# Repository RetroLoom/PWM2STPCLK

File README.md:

# PWM2STPCLK
Vintage CPU throttle adapter designed for use with interchangable PWM controllers. 

This project is inspired from the ThrottleBlaster project from Scrap Computing.

https://github.com/scrapcomputing/ThrottleBlaster

The PWM2STPCLK can mount directly to an ATX motherboard stand-off for direct chassis grounding and securing. This allows placement of the STPCLK pin wiring to be close to CPU and guarded from strain. A standard PWM fan controller can be used for simplicity, but plans for developing dedicated controllers and adapting the ThrottleBlaster is on-going. 

## Build of Materials
https://github.com/RetroLoom/PWM2STPCLK/blob/master/KiCad/PWM2STPCLK.csv

Example PWM Controller - https://www.aliexpress.us/item/3256805787442361.html?spm=a2g0o.order_list.order_list_main.71.628f1802pm9FhH&gatewayAdapt=glo2usa

Example PWM Cables - https://www.aliexpress.us/item/3256805588566722.html?spm=a2g0o.order_list.order_list_main.77.628f1802pm9FhH&gatewayAdapt=glo2usa

## Support the Developer
This project is brought to you free and open source, but it is not free to develop. If you like this project please consider supporting this and future developments. 

https://www.patreon.com/RetroLoom

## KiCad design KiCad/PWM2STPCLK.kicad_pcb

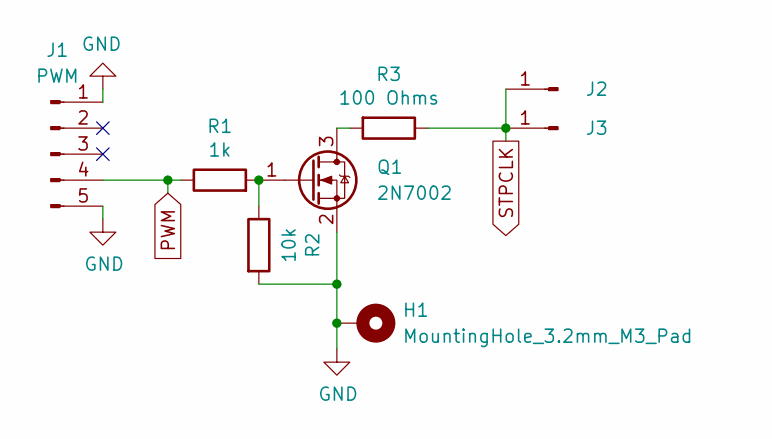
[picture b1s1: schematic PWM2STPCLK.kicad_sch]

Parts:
H1: MountingHole_3.2mm_M3_Pad
J1: PWM; PinSocket_1x05_P2.54mm_Vertical
J2, J3: STPCLK; PinHeader_1x01_P2.54mm_Horizontal
Q1: 2N7002; SOT-23
R1: 1k; R_0805_2012Metric
R2: 10k; R_0805_2012Metric
R3: 100 Ohms; R_0805_2012Metric

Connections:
GND: H1.1, J1.1, J1.5, Q1.2 (S), R2.2
unnamed: Q1.3 (D), R3.2
unnamed: Q1.1 (G), R1.2, R2.1
PWM: J1.4, R1.1
STPCLK: J2.1, J3.1, R3.1

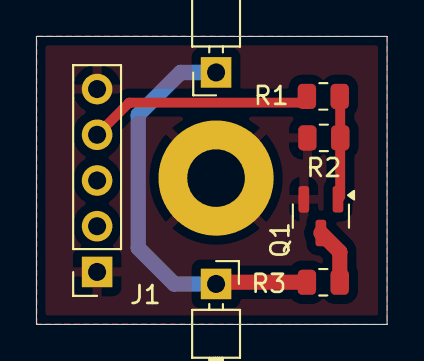
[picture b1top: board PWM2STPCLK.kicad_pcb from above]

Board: 2 copper layers, 19.5 x 16.0 mm, 8 parts (0 on the bottom side), 5 nets.

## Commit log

2025-01-30 Initial Release
2025-01-31 Update Readme, Images, License
2025-01-31 Fix broken readme images
2025-02-24 v0.2 - Low resistance ground, cleaner layout
2025-02-26 Fix CSV error
